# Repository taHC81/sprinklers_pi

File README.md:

# sprinklers_pi
Sprinklers Pi is a sophisticated Irrigation control system for the Raspberry Pi.  The system contains a built in mobile web page server that can be used to configure and monitor the system status from anywhere.  It can also be cross compiled on an AVR/Arduino platform with appropriate networking and storage hardware.

## Major Features
* Fully contained system with control logic and web serving.
* Same code can be compiled to run on the Atmel/AVR/Arduino platform.
* Web based control (including mobile Android iOS)
* Automatic adjustment of intervals based on weather conditions. (weather underground API)
* Weather conditions can be pulled from individual personal weather stations or from general weather data based on zipcode.
* Manual Control
* Scheduled Control
* Quick Schedule
* Named Zones
* Full Graphing feature of historic logs
* Ability to run with OpenSprinkler module or direct relay outputs.
* Supports master valve/pump output
* Supports expansion zone board (up to 15 zones)
* Very simple installation
* Seasonal adjustment.

## WiringPI for Orange Pi
Use the one from `https://github.com/zhaolei/WiringOP`

## Weather Setup
By default, we now ship with no weather provider enabled, and therefore no adjustment performed.
Follow the directions below to enable a weather provider. If you change weather providers be sure to run "make clean"
before rebuilding.

## Building
```Shell
make
sudo make install
```
NOTE: If you are running an older version of g++ compiler you may see the error `unrecognized command line option '-std=c++11'`. You should either update to g++ version 4.8+, or if you are not using DarkSky as a weather provider, you can remove `-std=c++11` at the end of line 8 in the Makefile. You can see what version of g++ you have by running `g++ --version`.

## Running
`sudo /etc/init.d/sprinklers_pi start`

See the wiki for more information: https://github.com/rszimm/sprinklers_pi/wiki

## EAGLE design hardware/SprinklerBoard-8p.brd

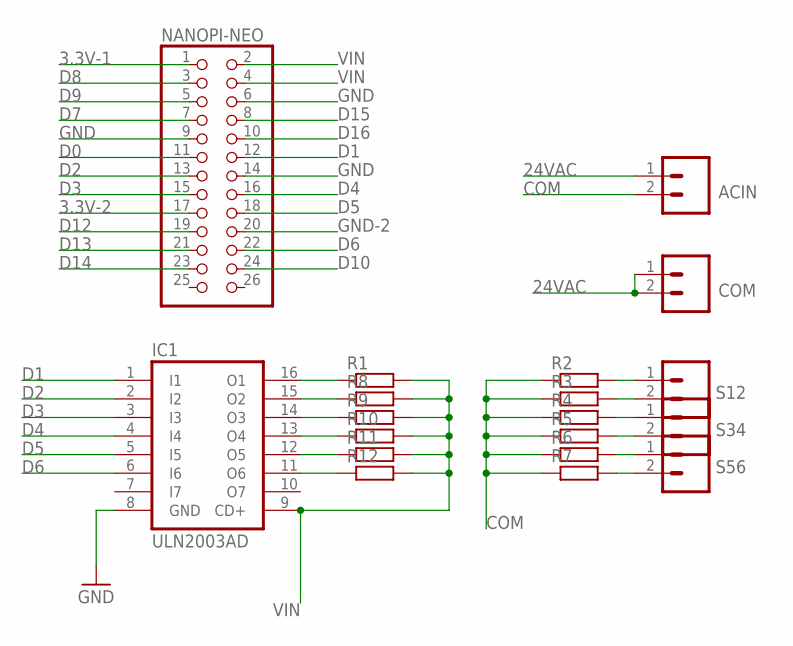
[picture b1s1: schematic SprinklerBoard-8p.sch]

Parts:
ACIN: M025MM-X; SCREWTERMINAL-5MM-2-X
COM: M025MM-X; SCREWTERMINAL-5MM-2-X
IC1: ULN2003AD; SO16
NANOPI-NEO: PINHD-2X13; 2X13
R1, R8, R9, R10, R11, R12: R-EU_0204/5; 0204/5
R2, R3, R4, R5, R6, R7: R-EU_0207/15; 0207/15
S12, S34, S56: M025MM-X; SCREWTERMINAL-5MM-2-X

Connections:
3.3V-1: NANOPI-NEO.1
3.3V-2: NANOPI-NEO.17
24VAC: ACIN.1, COM.1, COM.2
COM: ACIN.2, R2.1, R3.1, R4.1, R5.1, R6.1, R7.1
D0: NANOPI-NEO.11
D1: IC1.1 (I1), NANOPI-NEO.12
D2: IC1.2 (I2), NANOPI-NEO.13
D3: IC1.3 (I3), NANOPI-NEO.15
D4: IC1.4 (I4), NANOPI-NEO.16
D5: IC1.5 (I5), NANOPI-NEO.18
D6: IC1.6 (I6), NANOPI-NEO.22
D7: NANOPI-NEO.7
D8: NANOPI-NEO.3
D9: NANOPI-NEO.5
D10: NANOPI-NEO.24
D12: NANOPI-NEO.19
D13: NANOPI-NEO.21
D14: NANOPI-NEO.23
D15: NANOPI-NEO.8
D16: NANOPI-NEO.10
GND: IC1.8 (GND), NANOPI-NEO.6, NANOPI-NEO.9, NANOPI-NEO.14
GND-2: NANOPI-NEO.20
unnamed: R2.2, S12.1
unnamed: R3.2, S12.2
unnamed: R4.2, S34.1
unnamed: R5.2, S34.2
unnamed: R6.2, S56.1
unnamed: R7.2, S56.2
unnamed: IC1.16 (O1), R1.1
unnamed: IC1.15 (O2), R8.1
unnamed: IC1.14 (O3), R9.1
unnamed: IC1.13 (O4), R10.1
unnamed: IC1.12 (O5), R11.1
unnamed: IC1.11 (O6), R12.1
VIN: IC1.9 (CD+), NANOPI-NEO.2, NANOPI-NEO.4, R1.2, R8.2, R9.2, R10.2, R11.2, R12.2

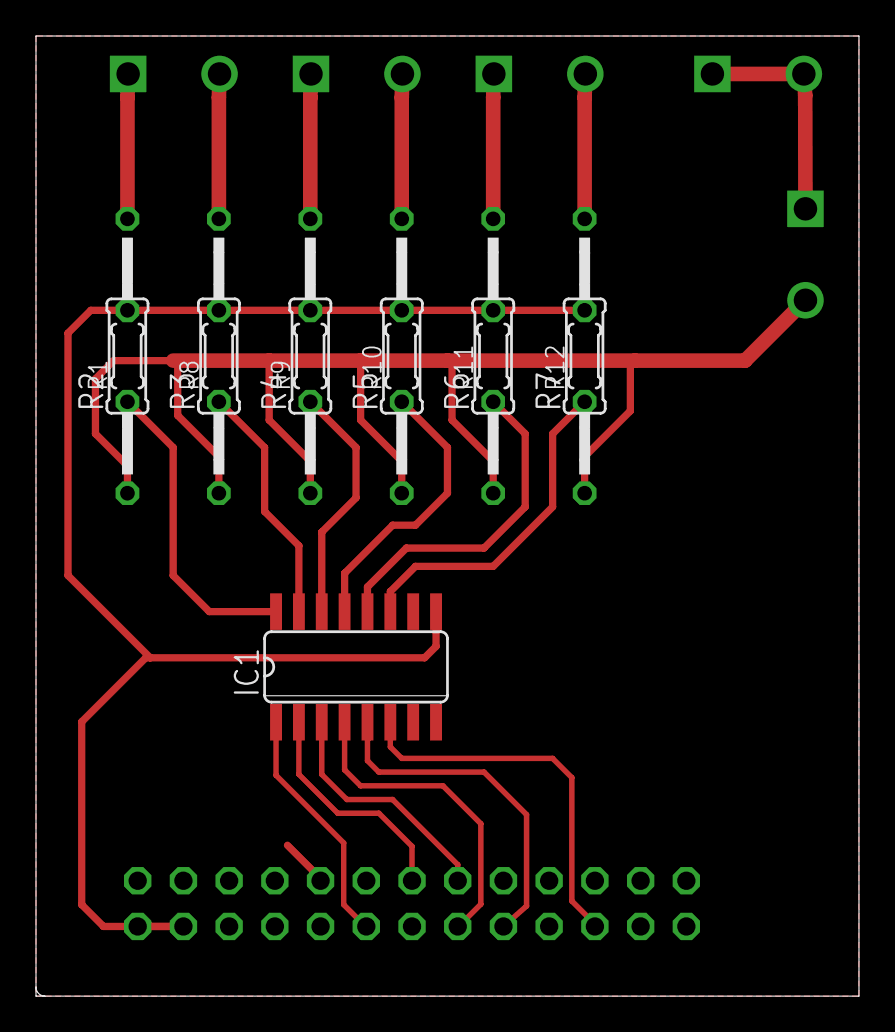
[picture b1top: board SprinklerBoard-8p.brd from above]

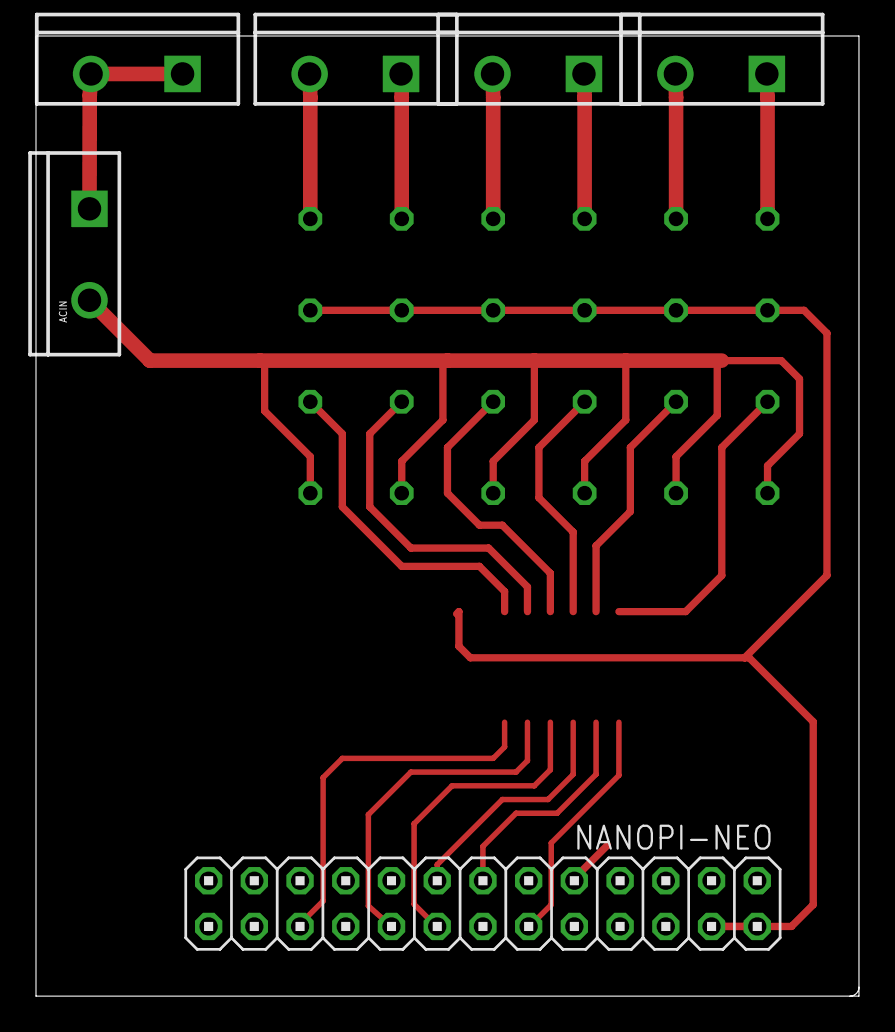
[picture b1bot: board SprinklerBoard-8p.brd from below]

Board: 2 copper layers, 45.7 x 53.3 mm, 19 parts (6 on the bottom side), 22 nets.

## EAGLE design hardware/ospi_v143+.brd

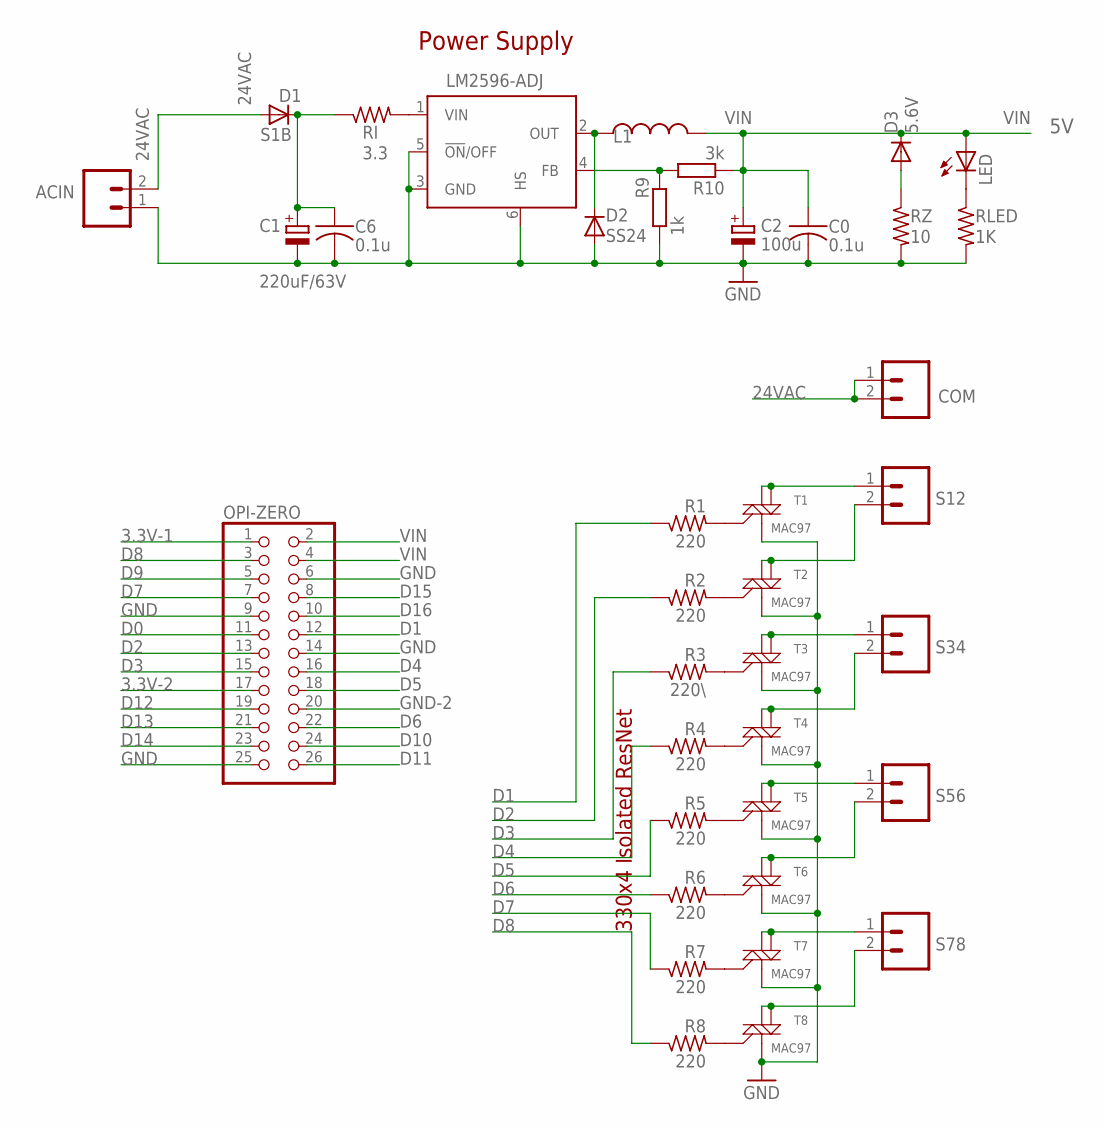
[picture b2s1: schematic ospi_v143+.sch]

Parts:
ACIN: M025MM-X; SCREWTERMINAL-5MM-2-X
C0, C6: 0.1u; C1206
C1: 220uF/63V; PANASONIC_E
C2: 100u; PANASONIC_E
COM: M025MM-X; SCREWTERMINAL-5MM-2-X
D1: S1B; DO-214AC
D2: SS24; SMB
D3: 5.6V; MINIMELF
L1: 150uH; CDRH125
LED: LEDCHIPLED_0805; CHIPLED_0805
LM2596-ADJ: LM2596-ADJ; TO263-5
OPI-ZERO: PINHD-2X13; 2X13
R1, R2, R4, R5, R6, R7, R8: 220; R0603
R3: 220\; R0603
R9: 1k; M0805
R10: 3k; M0805
RI: 3.3; R2010
RLED: 1K; R1206
RZ: 10; R2010
S12, S34, S56, S78: M025MM-X; SCREWTERMINAL-5MM-2-X
T1, T2, T3, T4, T5, T6, T7, T8: MAC97; SOT223

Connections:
3.3V-1: OPI-ZERO.1
3.3V-2: OPI-ZERO.17
24VAC: ACIN.2, COM.1, COM.2, D1.A
D0: OPI-ZERO.11
D1: OPI-ZERO.12, R1.1
D2: OPI-ZERO.13, R2.1
D3: OPI-ZERO.15, R3.1
D4: OPI-ZERO.16, R4.1
D5: OPI-ZERO.18, R5.1
D6: OPI-ZERO.22, R6.1
D7: OPI-ZERO.7, R7.1
D8: OPI-ZERO.3, R8.1
D9: OPI-ZERO.5
D10: OPI-ZERO.24
D11: OPI-ZERO.26
D12: OPI-ZERO.19
D13: OPI-ZERO.21
D14: OPI-ZERO.23
D15: OPI-ZERO.8
D16: OPI-ZERO.10
GND: ACIN.1, C0.2, C1.-, C2.-, C6.2, D2.A, LM2596-ADJ.3 (GND), LM2596-ADJ.5 (!ON!/OFF), LM2596-ADJ.6 (HS), OPI-ZERO.6, OPI-ZERO.9, OPI-ZERO.14, OPI-ZERO.25, R9.1, RLED.2, RZ.2, T1.1 (M1), T2.1 (M1), T3.1 (M1), T4.1 (M1), T5.1 (M1), T6.1 (M1), T7.1 (M1), T8.1 (M1)
GND-2: OPI-ZERO.20
unnamed: LED.C, RLED.1
unnamed: C1.+, C6.1, D1.C, RI.1
unnamed: R1.2, T1.3 (G)
unnamed: LM2596-ADJ.4 (FB), R9.2, R10.2
unnamed: D3.A, RZ.1
unnamed: D2.C, L1.1, LM2596-ADJ.2 (OUT)
unnamed: R2.2, T2.3 (G)
unnamed: S12.1, T1.2 (M2), T1.4 (M2-4)
unnamed: S12.2, T2.2 (M2), T2.4 (M2-4)
unnamed: S34.1, T3.2 (M2), T3.4 (M2-4)
unnamed: R3.2, T3.3 (G)
unnamed: S34.2, T4.2 (M2), T4.4 (M2-4)
unnamed: R4.2, T4.3 (G)
unnamed: S56.1, T5.2 (M2), T5.4 (M2-4)
unnamed: S56.2, T6.2 (M2), T6.4 (M2-4)
unnamed: S78.1, T7.2 (M2), T7.4 (M2-4)
unnamed: S78.2, T8.2 (M2), T8.4 (M2-4)
unnamed: R5.2, T5.3 (G)
unnamed: R6.2, T6.3 (G)
unnamed: R7.2, T7.3 (G)
unnamed: R8.2, T8.3 (G)
unnamed: LM2596-ADJ.1 (VIN), RI.2
VIN: C0.1, C2.+, D3.C, L1.2, LED.A, OPI-ZERO.2, OPI-ZERO.4, R10.1

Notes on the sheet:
Power Supply
330x4 Isolated ResNet

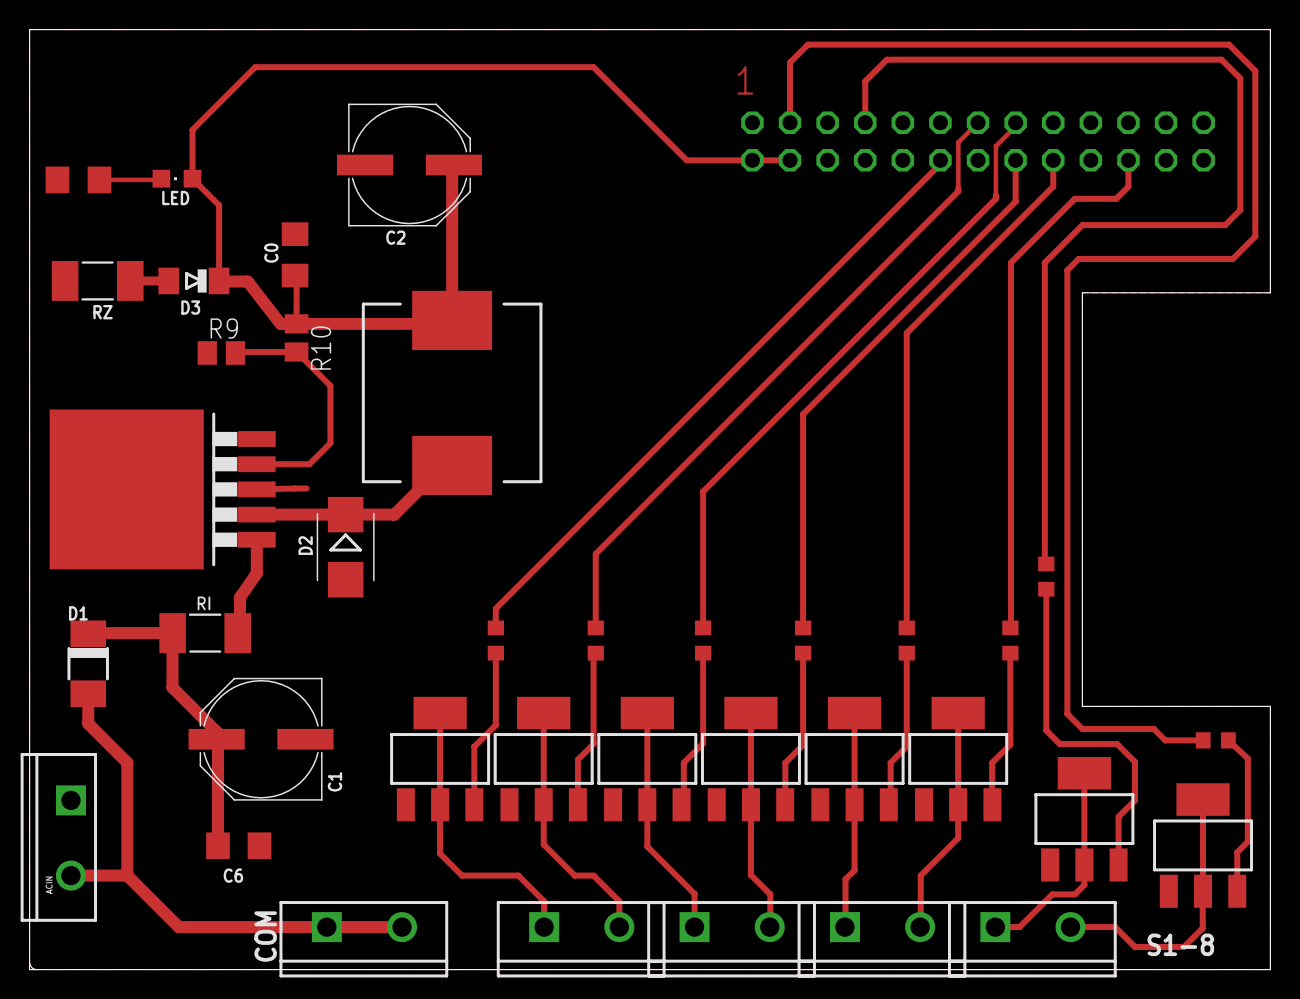
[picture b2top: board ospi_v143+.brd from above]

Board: 2 copper layers, 83.8 x 63.5 mm, 38 parts (1 on the bottom side), 33 nets.

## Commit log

2019-03-25 Create test
2019-03-25 Add files via upload
    Schematic - export from Eagle
2019-03-25 Revert "Update Weather.cpp"
    This reverts commit 19c375f8df912f813bd4ef422f1bef54a3bcf3be.
2019-03-25 Revert "Update Weather.cpp"
    This reverts commit 17bb9ba78c3ba4745afa413d496418bed250b99e.
2019-03-25 Revert "Update Weather.cpp"
    This reverts commit 735193731dd0270c8c755608e7e344bed61382b1.
2019-03-25 Revert "Update Weather.cpp"
    This reverts commit dbfcfa68205a1552454aff9367bf96200db6fc78.
2019-03-25 Revert "Update Weather.cpp"
    This reverts commit 4e8aef0d4f9a275e05ab03f7f987863b0eb159b0.
2019-03-25 Revert "Update WCheck.htm"
    This reverts commit cdf94ddffc0a4f552464a7e93aa2e3e1dd79913c.
2019-04-01 working from nanoPi
2019-04-01 New HW revision
2019-04-01 HW update
2019-04-03 wind
2019-04-03 new text
2019-04-03 Cancel watering when windy
2019-04-04 logic change
2019-04-04 Cleanup
2019-04-04 Logs updated
2019-04-17 adding prototype photos
2019-04-20 new photos
2019-04-22 Update Weather.cpp
    Skip watering if windy
